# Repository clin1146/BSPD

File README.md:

# Brake System Plausibility Device (BSPD)

**Manchester Stinger Motorsports** · Rev V4.0

The BSPD is a **non-programmable safety circuit**, implemented entirely in discrete
logic with **no microcontroller anywhere in the fault-detection or shutdown path**.
It continuously monitors the throttle position sensor (TPS) and brake pressure
sensor (BPS) and cuts power to the vehicle if either reports an implausible
condition.

---

## Fault conditions

### 1. Simultaneous brake and throttle
If the BPS indicates the brakes are applied while the TPS reads **more than 25 %
above idle position**, and both conditions persist continuously for **500 ms**, the
circuit cuts power to the vehicle.

### 2. Sensor signal out of range
If either the TPS or BPS signal falls outside the expected **0.5 V – 4.5 V** range
for **500 ms** — indicating a wiring fault, sensor failure, or an open or short
circuit — the circuit cuts power.

---

## Reset behaviour

Once the fault condition is no longer true, a 10-second timer starts. If no fault
recurs within that 10-second window, power resets automatically. If a fault recurs
during the window, the timer restarts, so power stays cut until a full 10 seconds
passes with no fault present.

---

## Functional block diagram

![BSPD functional block diagram: the BPS and TPS sensor signals feed an AND stage
(simultaneous brake and throttle); its output is OR'd with the SCS signal, which
flags either sensor leaving the 0.5–4.5 V range. The combined fault passes through
a 500 ms RC delay that latches Power Off, and drives an inverter into a 555-based
10 s timer that restores Power On once the fault has been clear for the full
window.](docs/system-block-diagram.png)

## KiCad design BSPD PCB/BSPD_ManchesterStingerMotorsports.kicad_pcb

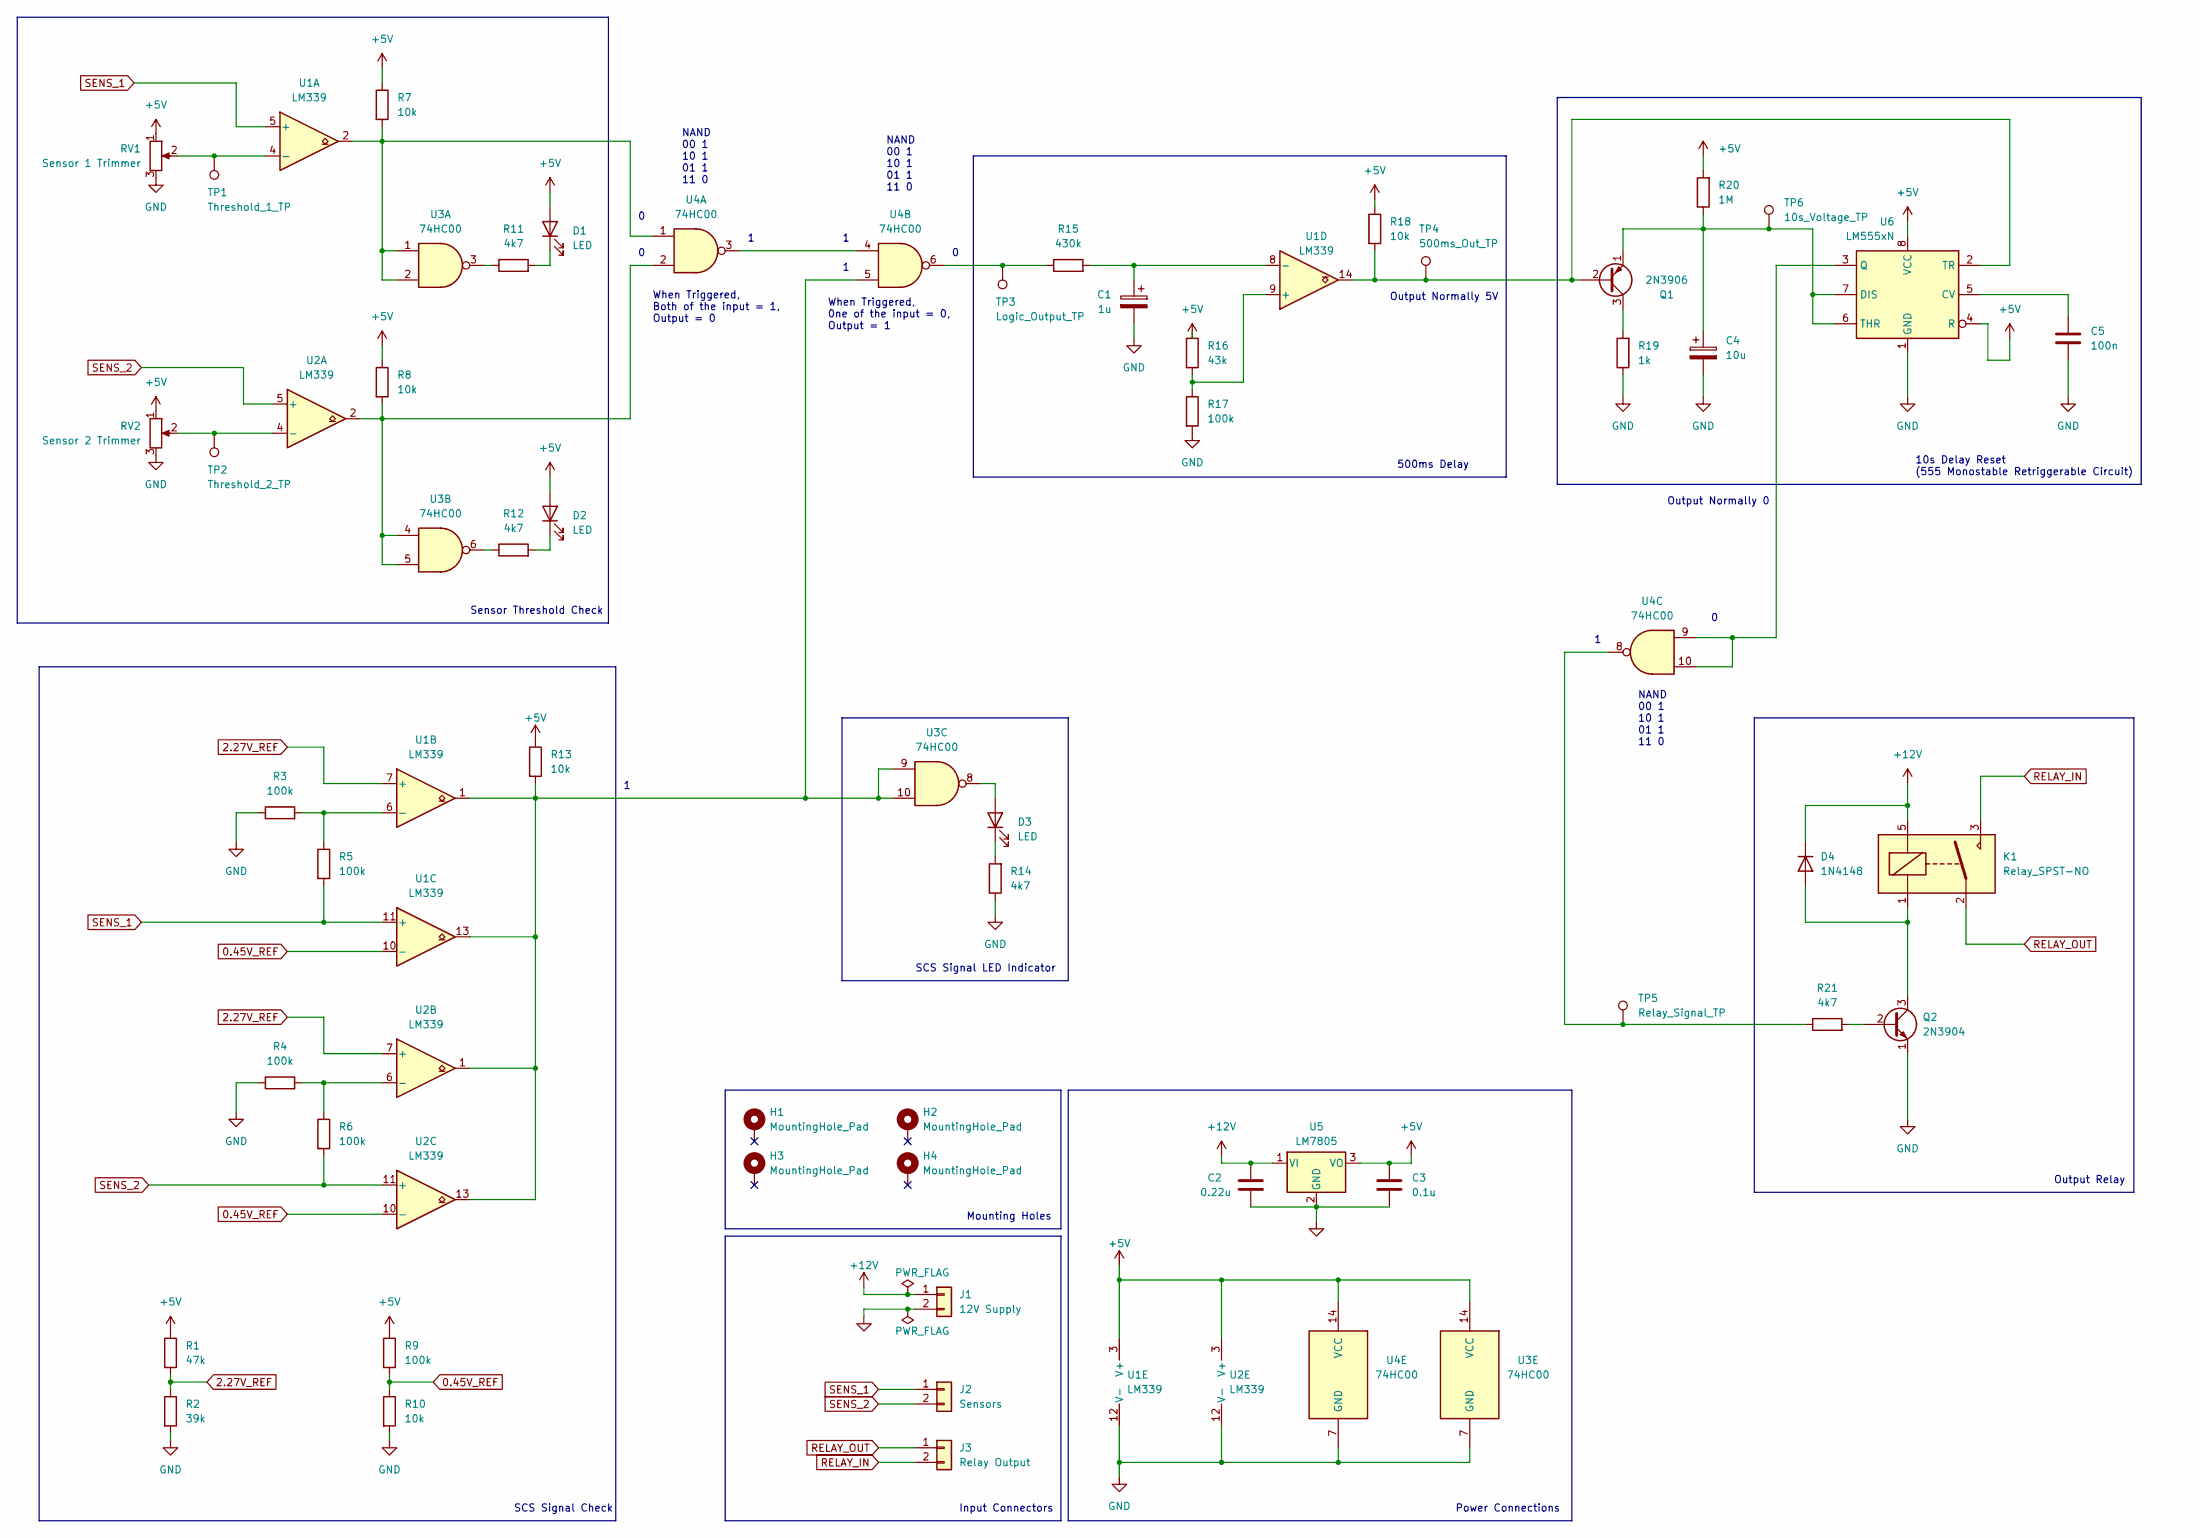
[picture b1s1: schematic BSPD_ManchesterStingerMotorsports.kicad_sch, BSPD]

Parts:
C1: 1u; CP_Radial_D5.0mm_P2.00mm
C2: 0.22u; C_Disc_D8.0mm_W2.5mm_P5.00mm
C3: 0.1u; C_Disc_D8.0mm_W2.5mm_P5.00mm
C4: 10u; CP_Radial_D5.0mm_P2.00mm
C5: 100n; C_Disc_D8.0mm_W2.5mm_P5.00mm
D1, D2, D3: LED; LED_D3.0mm
D4: 1N4148; D_DO-35_SOD27_P7.62mm_Horizontal
H1, H2, H3, H4: MountingHole_Pad; MountingHole_3.2mm_M3_DIN965_Pad
J1: 12V Supply; JST_VH_B2P-VH-FB-B_1x02_P3.96mm_Vertical
J2: Sensors; TerminalBlock_Phoenix_MPT-0,5-2-2.54_1x02_P2.54mm_Horizontal
J3: Relay Output; JST_VH_B2P-VH-FB-B_1x02_P3.96mm_Vertical
K1: Relay_SPST-NO; ALQ305
Q1: 2N3906; TO-92L_Wide
Q2: 2N3904; TO-92L_Wide
R1: 47k; R_Axial_DIN0207_L6.3mm_D2.5mm_P10.16mm_Horizontal
R2: 39k; R_Axial_DIN0207_L6.3mm_D2.5mm_P10.16mm_Horizontal
R3, R4, R5, R6, R9, R17: 100k; R_Axial_DIN0207_L6.3mm_D2.5mm_P10.16mm_Horizontal
R7, R8, R10, R13, R18: 10k; R_Axial_DIN0207_L6.3mm_D2.5mm_P10.16mm_Horizontal
R11, R12, R14, R21: 4k7; R_Axial_DIN0207_L6.3mm_D2.5mm_P10.16mm_Horizontal
R15: 430k; R_Axial_DIN0207_L6.3mm_D2.5mm_P10.16mm_Horizontal
R16: 43k; R_Axial_DIN0207_L6.3mm_D2.5mm_P10.16mm_Horizontal
R19: 1k; R_Axial_DIN0207_L6.3mm_D2.5mm_P10.16mm_Horizontal
R20: 1M; R_Axial_DIN0207_L6.3mm_D2.5mm_P10.16mm_Horizontal
RV1: Sensor 1 Trimmer; Potentiometer_Bourns_3386P_Vertical
RV2: Sensor 2 Trimmer; Potentiometer_Bourns_3386P_Vertical
TP1: Threshold_1_TP; TestPoint_Loop_D1.80mm_Drill1.0mm_Beaded
TP2: Threshold_2_TP; TestPoint_Loop_D1.80mm_Drill1.0mm_Beaded
TP3: Logic_Output_TP; TestPoint_Loop_D1.80mm_Drill1.0mm_Beaded
TP4: 500ms_Out_TP; TestPoint_Loop_D1.80mm_Drill1.0mm_Beaded
TP5: Relay_Signal_TP; TestPoint_Loop_D1.80mm_Drill1.0mm_Beaded
TP6: 10s_Voltage_TP; TestPoint_Loop_D1.80mm_Drill1.0mm_Beaded
U1, U2: LM339; DIP-14_W7.62mm
U3, U4: 74HC00; DIP-14_W7.62mm
U5: LM7805; TO-220-3_Horizontal_TabDown
U6: LM555xN; DIP-8_W7.62mm

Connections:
0.45V_REF: R9.2, R10.1, U1.10 (-), U2.10 (-)
2.27V_REF: R1.2, R2.1, U1.7 (+), U2.7 (+)
+5V: C3.1, D1.2 (A), D2.2 (A), R1.1, R7.1, R8.1, R9.1, R13.1, R16.1, R18.1, R20.2, RV1.1, RV2.1, U1.3 (V+), U2.3 (V+), U3.14 (VCC), U4.14 (VCC), U5.3 (VO), U6.4 (R), U6.8 (VCC)
+12V: C2.1, D4.1 (K), J1.1, K1.5, U5.1 (VI)
GND: C1.2, C2.2, C3.2, C4.2, C5.2, J1.2, Q2.1 (E), R2.2, R3.1, R4.1, R10.2, R14.1, R17.2, R19.1, RV1.3, RV2.3, U1.12 (V-), U2.12 (V-), U3.7 (GND), U4.7 (GND), U5.2 (GND), U6.1 (GND)
unnamed: D1.1 (K), R11.2
unnamed: D2.1 (K), R12.2
unnamed: D3.2 (A), U3.8
unnamed: D3.1 (K), R14.2
unnamed: D4.2 (A), K1.1, Q2.3 (C)
unnamed: Q1.2 (B), R18.2, TP4.1, U1.14, U6.2 (TR)
unnamed: Q1.3 (C), R19.2
unnamed: C4.1, Q1.1 (E), R20.1, TP6.1, U6.6 (THR), U6.7 (DIS)
unnamed: Q2.2 (B), R21.2
unnamed: R7.2, U1.2, U3.1, U3.2, U4.1
unnamed: R8.2, U2.2, U3.4, U3.5, U4.2
unnamed: R11.1, U3.3
unnamed: R12.1, U3.6
unnamed: R13.2, U1.1, U1.13, U2.1, U2.13, U3.9, U3.10, U4.5
unnamed: R15.1, TP3.1, U4.6
unnamed: R21.1, TP5.1, U4.8
unnamed: RV1.2, TP1.1, U1.4 (-)
unnamed: R3.2, R5.1, U1.6 (-)
unnamed: R16.2, R17.1, U1.9 (+)
unnamed: C1.1, R15.2, U1.8 (-)
unnamed: RV2.2, TP2.1, U2.4 (-)
unnamed: R4.2, R6.1, U2.6 (-)
unnamed: U4.3, U4.4
unnamed: C5.1, U6.5 (CV)
unnamed: U4.9, U4.10, U6.3 (Q)
RELAY_IN: J3.2, K1.3
RELAY_OUT: J3.1, K1.2
SENS_1: J2.1, R5.2, U1.5 (+), U1.11 (+)
SENS_2: J2.2, R6.2, U2.5 (+), U2.11 (+)

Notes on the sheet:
SCS Signal Check
When Triggered, Both of the input = 1, Output = 0
500ms Delay
Mounting Holes
Output Relay
SCS Signal LED Indicator
Power Connections
NAND 00 1 10 1 01 1 11 0
Sensor Threshold Check
Output Normally 5V
Input Connectors
When Triggered, 0ne of the input = 0, Output = 1
10s Delay Reset (555 Monostable Retriggerable Circuit)
Output Normally 0

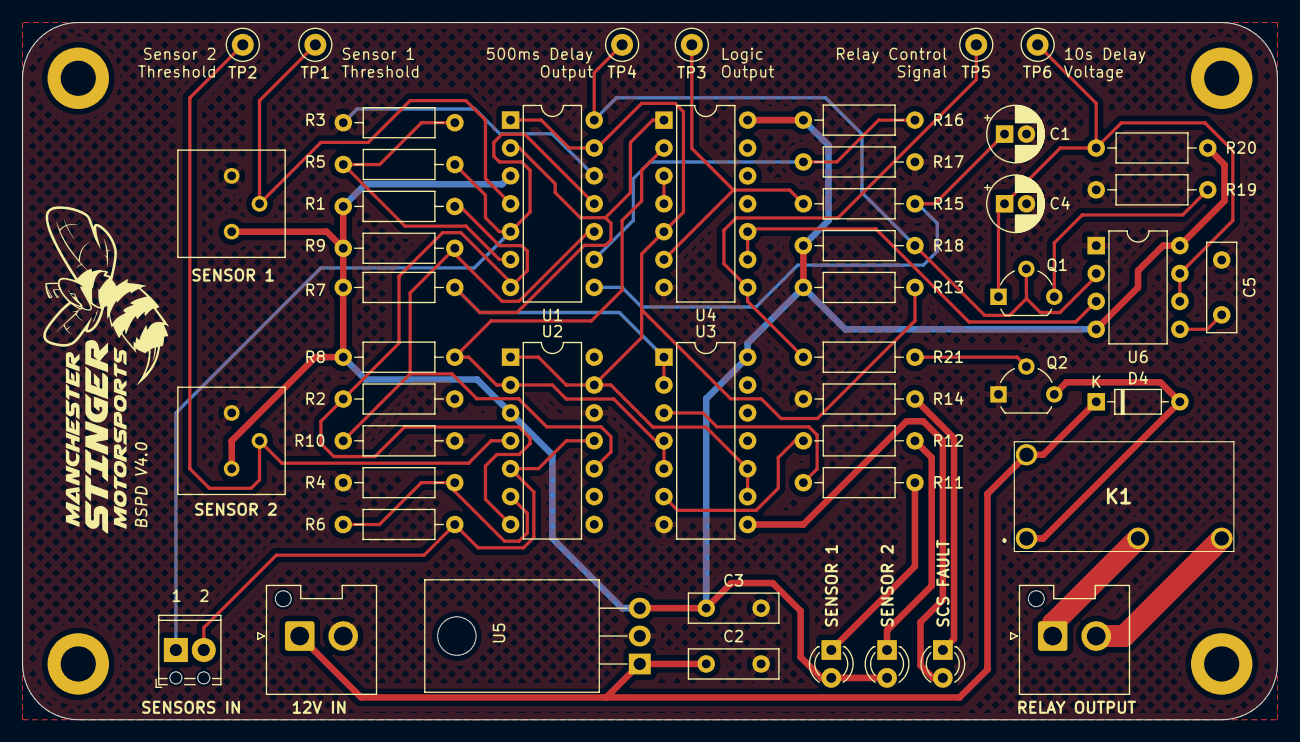
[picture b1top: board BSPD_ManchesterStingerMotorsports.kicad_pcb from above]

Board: 2 copper layers, 114.3 x 63.5 mm, 54 parts (0 on the bottom side), 34 nets.
